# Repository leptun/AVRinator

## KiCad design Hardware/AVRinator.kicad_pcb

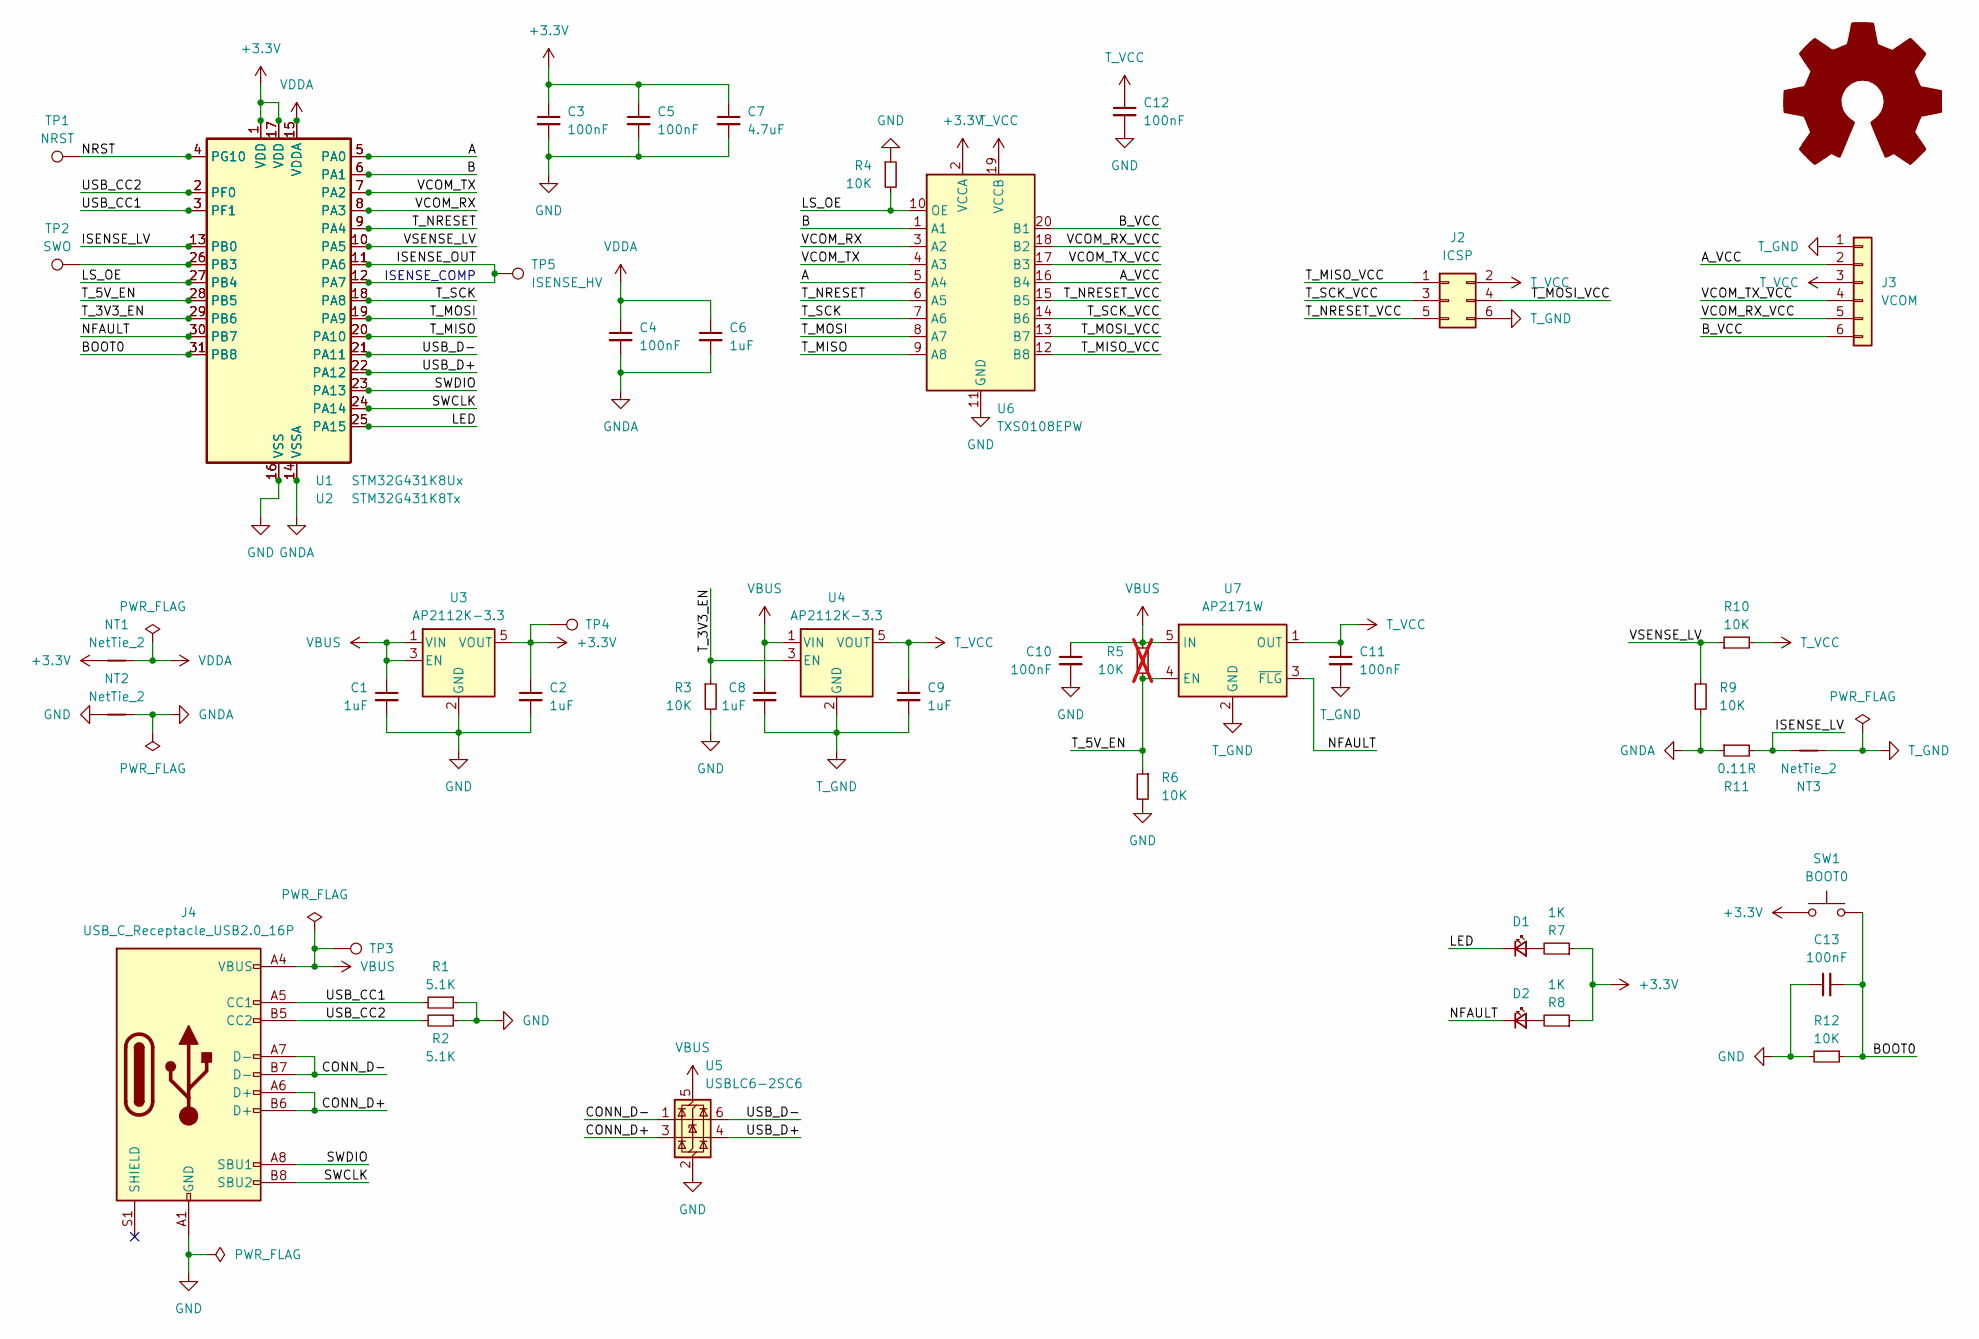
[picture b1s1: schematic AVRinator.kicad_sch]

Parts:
C1, C2, C6, C8, C9: 1uF; C_0805_2012Metric
C3, C4, C5, C10, C11, C12, C13: 100nF; C_0603_1608Metric
C7: 4.7uF; C_1206_3216Metric
D1, D2: LED_1206_3216Metric
J2: ICSP; 61200621621
J3: VCOM; PinSocket_1x06_P2.54mm_Horizontal
J4: USB_C_Receptacle_USB2.0_16P; USB4110-GF-A
NT1, NT2, NT3: NetTie_2; NetTie-2_SMD_Pad0.5mm
R1, R2: 5.1K; R_0603_1608Metric
R3, R4, R6, R9, R10, R12: 10K; R_0603_1608Metric
R5: 10K; R_0603_1608Metric; not fitted
R7, R8: 1K; R_0805_2012Metric
R11: 0.11R; R_0805_2012Metric
SW1: BOOT0; SW_Tactile_SPST_NO_Straight_CK_PTS636Sx25SMTRLFS
SYM1: AMOGUS; AMOGUS_lil
TP1: NRST; TestPoint_Pad_D1.0mm
TP2: SWO; TestPoint_Pad_D1.0mm
TP3: VBUS; TestPoint_Pad_D1.0mm
TP4: 3V3; TestPoint_Pad_D1.0mm
TP5: ISENSE_HV; TestPoint_Pad_D1.0mm
U1: STM32G431K8Ux; QFN-32-1EP_5x5mm_P0.5mm_EP3.45x3.45mm
U2: STM32G431K8Tx; LQFP-32_7x7mm_P0.8mm
U3, U4: AP2112K-3.3; SOT-23-5
U5: USBLC6-2SC6; SOT-23-6
U6: TXS0108EPW; TSSOP-20_4.4x6.5mm_P0.65mm
U7: AP2171W; SOT-23-5

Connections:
+3.3V: C2.1, C3.1, C5.1, C7.1, NT1.1, R7.1, R8.1, SW1.1, TP4.1, U1.1 (VDD), U1.17 (VDD), U2.1 (VDD), U2.17 (VDD), U3.5 (VOUT), U6.2 (VCCA)
/A: U1.5 (PA0), U2.5 (PA0), U6.5 (A4)
/A_VCC: J3.2, U6.16 (B4)
/B: U1.6 (PA1), U2.6 (PA1), U6.1 (A1)
/BOOT0: C13.2, R12.1, SW1.2, U1.31 (PB8), U2.31 (PB8)
/B_VCC: J3.6, U6.20 (B1)
/CONN_D+: J4.A6 (D+), J4.B6 (D+), U5.3 (I/O2)
/CONN_D-: J4.A7 (D-), J4.B7 (D-), U5.1 (I/O1)
/ISENSE_LV: NT3.1, R11.2, U1.13 (PB0), U2.13 (PB0)
/ISENSE_OUT: TP5.1, U1.11 (PA6), U1.12 (PA7), U2.11 (PA6), U2.12 (PA7)
/LED: D1.1 (K), U1.25 (PA15), U2.25 (PA15)
/LS_OE: R4.2, U1.27 (PB4), U2.27 (PB4), U6.10 (OE)
/NFAULT: D2.1 (K), U1.30 (PB7), U2.30 (PB7), U7.3 (~FLG)
/NRST: TP1.1, U1.4 (PG10), U2.4 (PG10)
/SWCLK: J4.B8 (SBU2), U1.24 (PA14), U2.24 (PA14)
/SWDIO: J4.A8 (SBU1), U1.23 (PA13), U2.23 (PA13)
/T_3V3_EN: R3.1, U1.29 (PB6), U2.29 (PB6), U4.3 (EN)
/T_5V_EN: R5.1, R6.1, U1.28 (PB5), U2.28 (PB5), U7.4 (EN)
/T_MISO: U1.20 (PA10), U2.20 (PA10), U6.9 (A8)
/T_MISO_VCC: J2.1, U6.12 (B8)
/T_MOSI: U1.19 (PA9), U2.19 (PA9), U6.8 (A7)
/T_MOSI_VCC: J2.4, U6.13 (B7)
/T_NRESET: U1.9 (PA4), U2.9 (PA4), U6.6 (A5)
/T_NRESET_VCC: J2.5, U6.15 (B5)
/T_SCK: U1.18 (PA8), U2.18 (PA8), U6.7 (A6)
/T_SCK_VCC: J2.3, U6.14 (B6)
/USB_CC1: J4.A5 (CC1), R1.2, U1.3 (PF1), U2.3 (PF1)
/USB_CC2: J4.B5 (CC2), R2.2, U1.2 (PF0), U2.2 (PF0)
/USB_D+: U1.22 (PA12), U2.22 (PA12), U5.4 (I/O2)
/USB_D-: U1.21 (PA11), U2.21 (PA11), U5.6 (I/O1)
/VCOM_RX: U1.8 (PA3), U2.8 (PA3), U6.3 (A2)
/VCOM_RX_VCC: J3.5, U6.18 (B2)
/VCOM_TX: U1.7 (PA2), U2.7 (PA2), U6.4 (A3)
/VCOM_TX_VCC: J3.4, U6.17 (B3)
/VSENSE_LV: R9.1, R10.1, U1.10 (PA5), U2.10 (PA5)
GND: C1.2, C2.2, C3.2, C5.2, C7.2, C10.2, C12.2, C13.1, J4.A1 (GND), J4.A12 (GND), J4.B1 (GND), J4.B12 (GND), NT2.1, R1.1, R2.1, R3.2, R4.1, R6.2, R12.2, U1.16 (VSS), U1.32 (VSS), U1.33 (VSS), U2.16 (VSS), U2.32 (VSS), U3.2 (GND), U5.2 (GND), U6.11 (GND)
GNDA: C4.2, C6.2, NT2.2, R9.2, R11.1, U1.14 (VSSA), U2.14 (VSSA)
unnamed: D1.2 (A), R7.2
unnamed: D2.2 (A), R8.2
unnamed: TP2.1, U1.26 (PB3), U2.26 (PB3)
T_GND: C8.2, C9.2, C11.2, J2.6, J3.1, NT3.2, U4.2 (GND), U7.2 (GND)
T_VCC: C9.1, C11.1, C12.1, J2.2, J3.3, R10.2, U4.5 (VOUT), U6.19 (VCCB), U7.1 (OUT)
VBUS: C1.1, C8.1, C10.1, J4.A4 (VBUS), J4.A9 (VBUS), J4.B4 (VBUS), J4.B9 (VBUS), R5.2, TP3.1, U3.1 (VIN), U3.3 (EN), U4.1 (VIN), U5.5 (VBUS), U7.5 (IN)
VDDA: C4.1, C6.1, NT1.2, U1.15 (VDDA), U2.15 (VDDA)

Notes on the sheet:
ISENSE_COMP

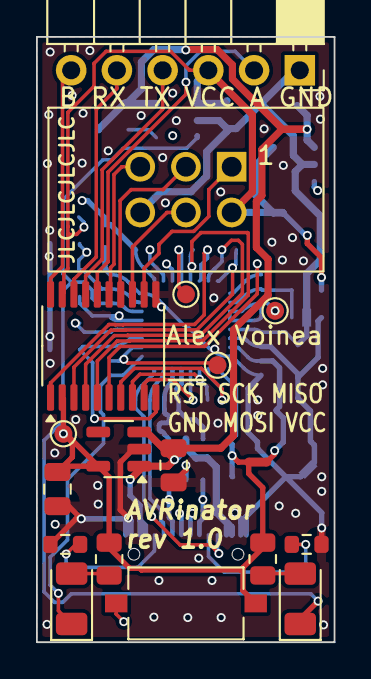
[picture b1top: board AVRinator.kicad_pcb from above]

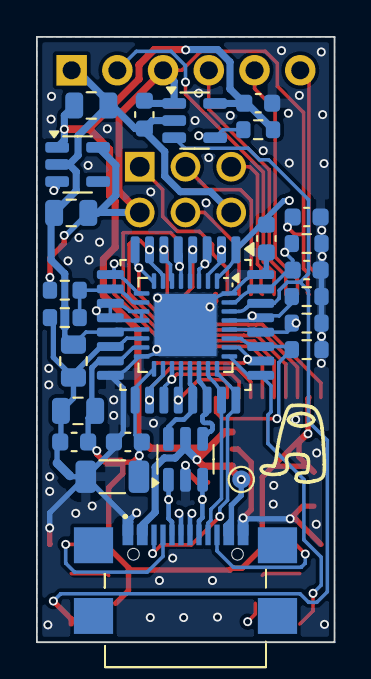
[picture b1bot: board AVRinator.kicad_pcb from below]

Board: 4 copper layers, 16.5 x 33.6 mm, 47 parts (29 on the bottom side), 44 nets.

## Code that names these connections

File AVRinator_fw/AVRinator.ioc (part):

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Mcu.Name=STM32G431K(6-8-B)Tx
Mcu.Package=LQFP32
Mcu.UserName=STM32G431K8Tx
PA0.GPIOParameters=GPIO_Speed,GPIO_Label
PA0.GPIO_Label=A
PA0.GPIO_Speed=GPIO_SPEED_FREQ_VERY_HIGH
PA0.Signal=SharedStack_PA0
PA0.Stacked=true
PA1.GPIOParameters=GPIO_Speed,GPIO_Label
PA1.GPIO_Label=B
PA1.GPIO_Speed=GPIO_SPEED_FREQ_VERY_HIGH
PA1.Signal=SharedStack_PA1
PA1.Stacked=true
PA10.GPIOParameters=GPIO_Speed,GPIO_PuPd,GPIO_Label
PA10.GPIO_Label=T_MISO
PA10.GPIO_PuPd=GPIO_NOPULL
PA10.GPIO_Speed=GPIO_SPEED_FREQ_VERY_HIGH
PA10.Mode=Synchronous
PA10.Signal=USART1_RX
PA11.Mode=Device
PA11.Signal=USB_DM
PA12.Mode=Device
PA12.Signal=USB_DP
PA13.Mode=Trace_Asynchronous_SW
PA13.Signal=SYS_JTMS-SWDIO
PA14.Mode=Trace_Asynchronous_SW
PA14.Signal=SYS_JTCK-SWCLK
PA15.GPIOParameters=PinState,GPIO_PuPd,GPIO_Label,GPIO_ModeDefaultOutputPP
PA15.GPIO_Label=LED
PA15.GPIO_ModeDefaultOutputPP=GPIO_MODE_OUTPUT_OD
PA15.GPIO_PuPd=GPIO_NOPULL
PA15.PinState=GPIO_PIN_SET
PA15.Signal=GPIO_Output
PA2.GPIOParameters=GPIO_Speed,GPIO_Label
PA2.GPIO_Label=VCOM_TX
PA2.GPIO_Speed=GPIO_SPEED_FREQ_VERY_HIGH
PA2.Mode=Asynchronous
PA2.Signal=USART2_TX
PA3.GPIOParameters=GPIO_Speed,GPIO_PuPd,GPIO_Label
PA3.GPIO_Label=VCOM_RX
PA3.GPIO_PuPd=GPIO_PULLUP
PA3.GPIO_Speed=GPIO_SPEED_FREQ_VERY_HIGH
PA3.Mode=Asynchronous
PA3.Signal=USART2_RX
PA4.GPIOParameters=GPIO_Speed,PinState,GPIO_PuPd,GPIO_Label,GPIO_ModeDefaultOutputPP
PA4.GPIO_Label=T_NRESET
PA4.GPIO_ModeDefaultOutputPP=GPIO_MODE_OUTPUT_OD
PA4.GPIO_PuPd=GPIO_NOPULL
PA4.GPIO_Speed=GPIO_SPEED_FREQ_VERY_HIGH
PA4.PinState=GPIO_PIN_SET
PA4.Signal=GPIO_Output
PA5.GPIOParameters=GPIO_Label
PA5.GPIO_Label=VSENSE_LV
PA5.Signal=SharedAnalog_PA5
PA6.GPIOParameters=GPIO_Label
PA6.GPIO_Label=ISENSE_OUT
PA6.Signal=SharedAnalog_PA6
PA7.GPIOParameters=GPIO_Label
PA7.GPIO_Label=ISENSE_COMP
PA7.Signal=SharedAnalog_PA7
PA8.GPIOParameters=GPIO_Speed,GPIO_Label
PA8.GPIO_Label=T_SCK
PA8.GPIO_Speed=GPIO_SPEED_FREQ_VERY_HIGH
PA8.Mode=Synchronous
PA8.Signal=USART1_CK
PA9.GPIOParameters=GPIO_Speed,GPIO_Label
PA9.GPIO_Label=T_MOSI
PA9.GPIO_Speed=GPIO_SPEED_FREQ_VERY_HIGH
PA9.Mode=Synchronous
PA9.Signal=USART1_TX
PB0.GPIOParameters=GPIO_Label
PB0.GPIO_Label=ISENSE_LV
PB0.Signal=SharedAnalog_PB0
PB3.Mode=Trace_Asynchronous_SW
PB3.Signal=SYS_JTDO-SWO
PB4.GPIOParameters=GPIO_Speed,GPIO_Label
PB4.GPIO_Label=LS_OE
PB4.GPIO_Speed=GPIO_SPEED_FREQ_VERY_HIGH
PB4.Signal=GPIO_Output
PB5.GPIOParameters=GPIO_Speed,GPIO_Label
PB5.GPIO_Label=T_5V_EN
PB5.GPIO_Speed=GPIO_SPEED_FREQ_VERY_HIGH
PB5.Signal=GPIO_Output
PB6.GPIOParameters=GPIO_Speed,GPIO_Label
PB6.GPIO_Label=T_3V3_EN
PB6.GPIO_Speed=GPIO_SPEED_FREQ_VERY_HIGH
PB6.Signal=GPIO_Output
PB7.GPIOParameters=GPIO_Speed,GPIO_PuPd,GPIO_Label
PB7.GPIO_Label=NFAULT
PB7.GPIO_PuPd=GPIO_NOPULL
PB7.GPIO_Speed=GPIO_SPEED_FREQ_VERY_HIGH
PB7.Signal=GPIO_Input
PB8-BOOT0.GPIOParameters=GPIO_Label
PB8-BOOT0.GPIO_Label=SW
PB8-BOOT0.Signal=GPIO_Input
PF0-OSC_IN.GPIOParameters=GPIO_Label
PF0-OSC_IN.GPIO_Label=USB_CC2
PF0-OSC_IN.Signal=SharedAnalog_PF0
PF1-OSC_OUT.GPIOParameters=GPIO_Label
PF1-OSC_OUT.GPIO_Label=USB_CC1
PF1-OSC_OUT.Signal=SharedAnalog_PF1
RCC.HSE_VALUE=8000000
RCC.SYSCLKFreq_VALUE=170000000
RCC.SYSCLKSource=RCC_SYSCLKSOURCE_PLLCLK
board=custom

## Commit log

2024-04-30 Add ISP header pinout
2024-04-30 Generate gerber files
2024-04-30 Fw initial
2024-04-30 remove freertos
2024-04-30 Add freertos back properly this time
2024-04-30 Initial project setup
2024-04-30 Make USB enumerate
2024-04-30 Some usb descriptor work
2024-05-01 Temporary vid pid workaround
2024-05-01 Add VENDOR EP0 empty class
2024-05-01 PAVR protocol initial
2024-05-01 PAVR restructure control callback stage handling
2024-05-02 Persistent settings initial
2024-05-02 Functional persistent settings
2024-05-02 Remove unnecessary nested struct
2024-05-02 Enable optimizations during debug for tinyusb
2024-05-02 TTL initial
2024-05-02 Update tinyusb
2024-05-02 fix eeprom initialization from empty
2024-05-02 provide string descriptor 6
2024-05-04 Temp broken ttl
2024-05-04 Fix CDC tx notification
2024-05-04 direct to task notifications usart
2024-05-04 Add TXS0108EPW decoupling cap and tune skew of usb
2024-05-04 Final touchups
2024-05-04 A bit more touchup
2024-05-04 Update gerber files
2024-05-04 Add JLCJLCJLCJLC incantation
2024-05-04 Extract constants to config
2024-05-04 CDC IN pumping instead of complete flush
2024-05-05 Finally TTL works reliably
2024-05-06 USART synchronous operation
2024-05-06 Enable the USART fifo
2024-05-06 Isp groundwork
2024-05-07 Update pin naming
2024-05-07 Memory restructuring
2024-05-07 Pin definitions
2024-05-07 Use static memory
2024-05-07 Functional yet again
2024-05-07 NMI parity error handler
2024-05-08 Use PAVR2 vid pid
2024-05-08 Power management initial
2024-05-11 AVRISP2 parser initial
2024-05-11 Implement all get param used by avrdude
2024-05-20 reorganize files in project
2024-05-21 Functional ISP prototype
2024-05-21 Command batching
2024-05-23 Timing fixes, uart fixes, eliminate isp bus contention
